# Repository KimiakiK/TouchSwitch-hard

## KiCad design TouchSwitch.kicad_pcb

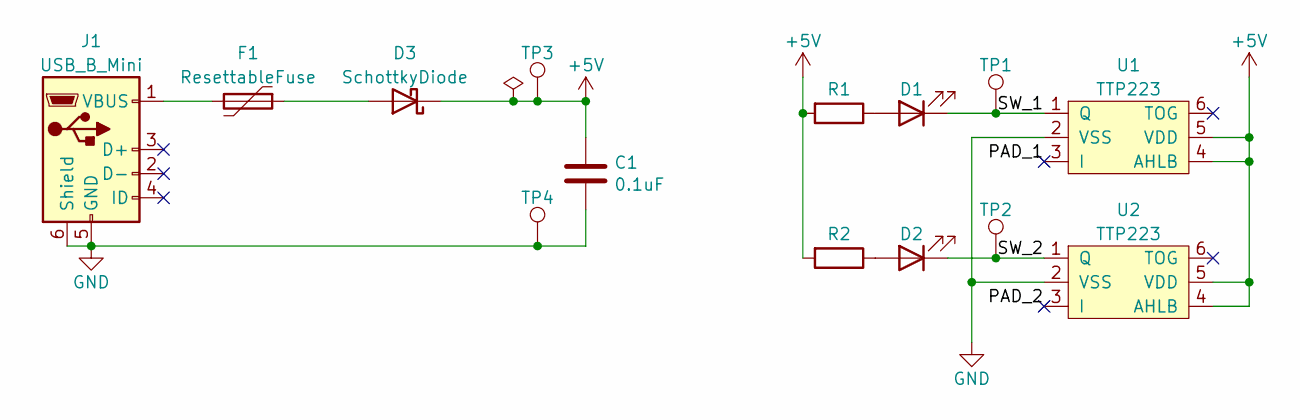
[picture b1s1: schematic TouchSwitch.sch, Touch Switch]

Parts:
C1: 0.1uF; 1608Metric
D1, D2: LED; 1608Metric
D3: SchottkyDiode; D_TUMD2
F1: ResettableFuse; 1608Metric
J1: USB_B_Mini; UX60SC-MB-5ST
R1, R2: R; 1608Metric
TP1, TP2, TP3, TP4: TestPoint; TestPoint_THTPad_D1.6mm_Drill1.0mm
U1, U2: TTP223; SOT-23-6

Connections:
+5V: C1.1, D3.1 (K), R1.2, R2.2, TP3.1, U1.4 (AHLB), U1.5 (VDD), U2.4 (AHLB), U2.5 (VDD)
/PAD_1: U1.3 (I)
/PAD_2: U2.3 (I)
/SW_1: D1.1 (K), TP1.1, U1.1 (Q)
/SW_2: D2.1 (K), TP2.1, U2.1 (Q)
GND: C1.2, J1.5 (GND), J1.6 (Shield), TP4.1, U1.2 (VSS), U2.2 (VSS)
unnamed: D1.2 (A), R1.1
unnamed: D2.2 (A), R2.1
unnamed: D3.2 (A), F1.1
unnamed: F1.2, J1.1 (VBUS)

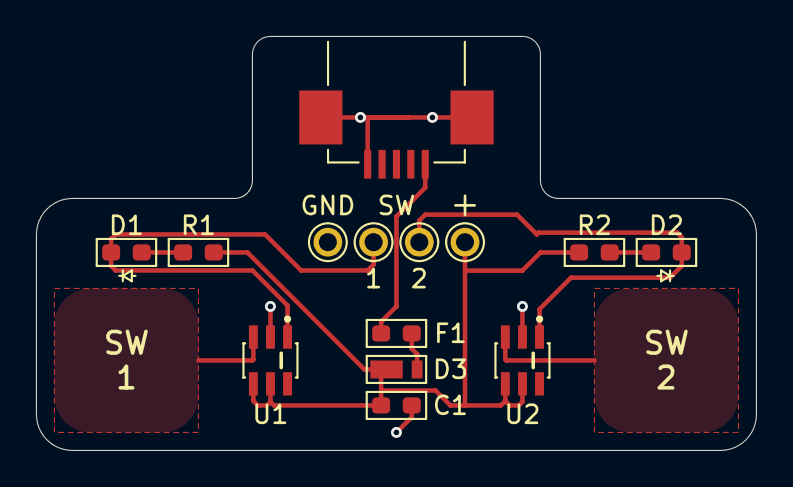
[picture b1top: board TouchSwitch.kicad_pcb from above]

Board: 2 copper layers, 40.0 x 23.0 mm, 14 parts (0 on the bottom side), 8 nets.

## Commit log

2021-07-10 基板 V1.0
